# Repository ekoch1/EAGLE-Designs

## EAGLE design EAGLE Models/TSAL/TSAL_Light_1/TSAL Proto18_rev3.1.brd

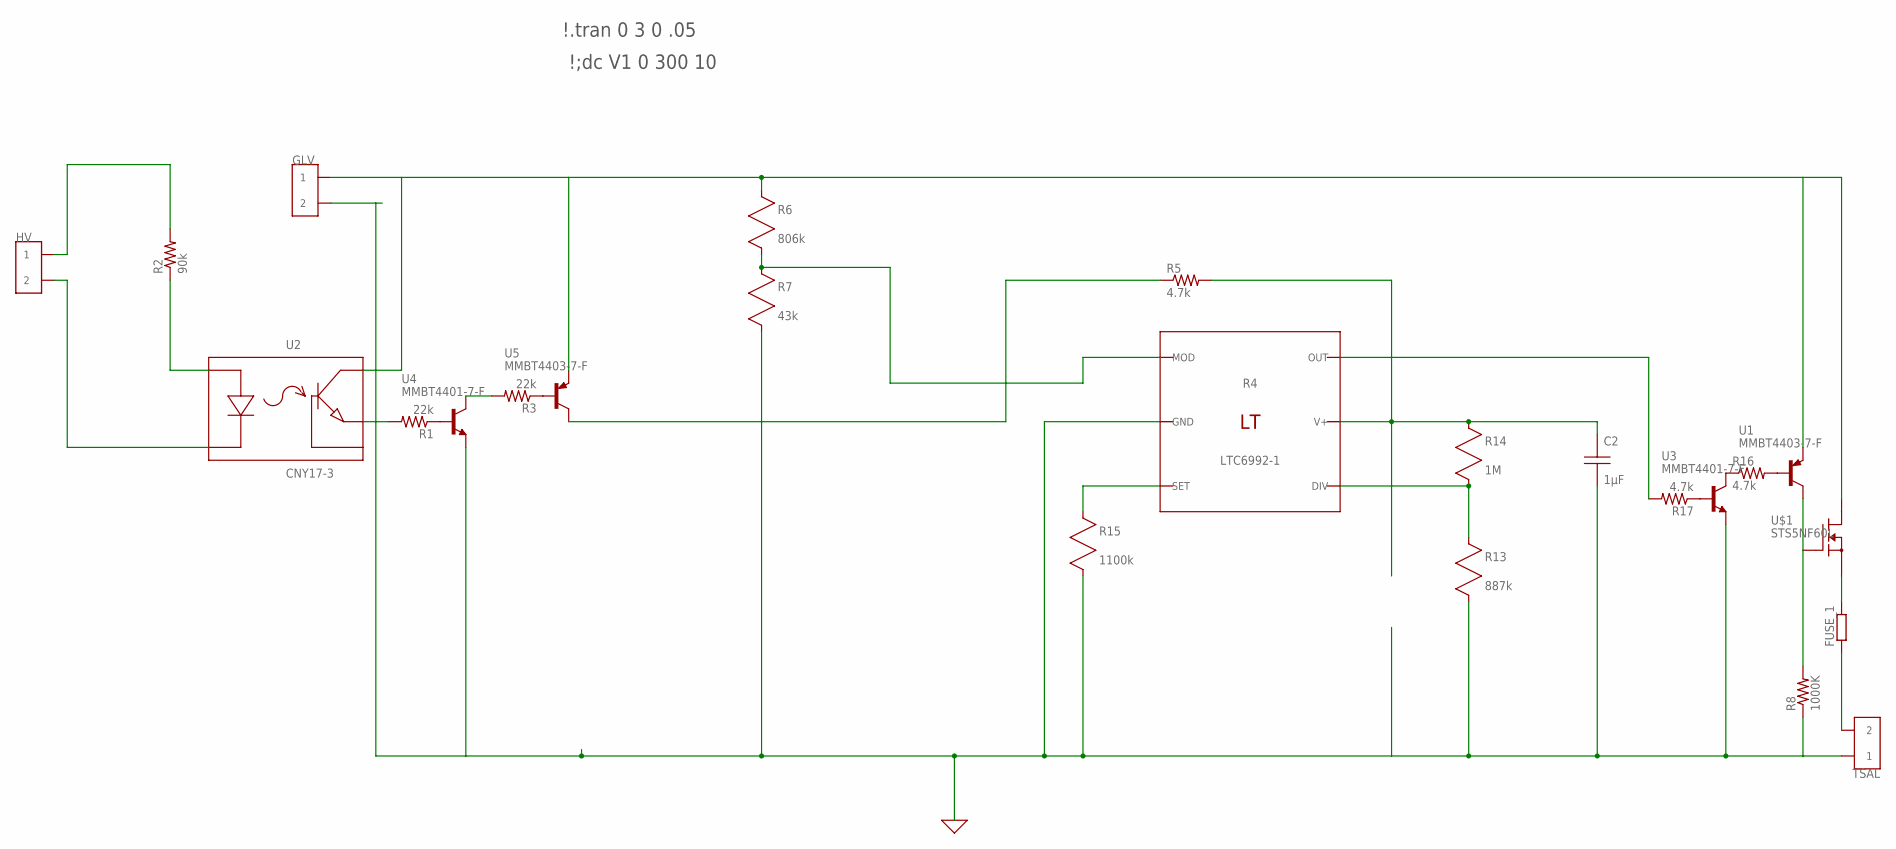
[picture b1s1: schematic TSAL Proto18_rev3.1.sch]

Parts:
C2: 1µF; C0805
FUSE_1: R-EU_R0402; R0402
GLV: CONN_2; CONNECTOR_2
HV: CONN_2; CONNECTOR_2
R1, R3: 22k; R0402
R2: 90k; P0817/22
R4: LTC6992-1
R5: 4.7k; 0805
R6: 806k; R0805
R7: 43k; R0805
R8: 1000K; 0805
R13: 887k; R0805
R14: 1M; R0805
R15: 1100k; R0805
R16, R17: 4.7k; R0402
TSAL: CONN_2; CONNECTOR_2
U1, U5: MMBT4403-7-F; SOT-23-3
U2: CNY17-3
U3, U4: MMBT4401-7-F; SOT-23-3
U$1: STS5NF60L; SO08

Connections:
12V: GLV.1, GLV.2 (1), R6.1 (A), U1.P$3 (E), U2.P$5 (C), U5.P$3 (E), U$1.5 (D), U$1.6 (D), U$1.7 (D), U$1.8 (D)
GND: C2.2 (B), GLV.3 (2), GLV.4 (2), R4.P$2 (GND), R7.2 (B), R8.1, R13.2 (B), R15.2 (B), TSAL.1, TSAL.2 (1), U3.P$3 (E), U4.P$3 (E)
HV+: HV.1, HV.2 (1), R2.2
HV-: HV.3 (2), HV.4 (2), U2.P$2 (K)
unnamed: R1.1, U4.P$2 (B)
unnamed: R3.1, U5.P$2 (B)
unnamed: R3.2, U4.P$1 (C)
unnamed: R1.2, U2.P$4 (E)
unnamed: R5.1, U5.P$1 (C)
unnamed: R8.2, U1.P$1 (C), U$1.4 (G)
unnamed: R4.P$1 (MOD), R6.2 (B), R7.1 (A)
unnamed: R4.P$6 (OUT), R17.2
unnamed: R2.1, U2.P$1 (A)
unnamed: FUSE_1.2, U$1.1 (S), U$1.2 (S), U$1.3 (S)
unnamed: R16.2, U1.P$2 (B)
unnamed: R16.1, U3.P$1 (C)
unnamed: C2.1 (A), R4.P$5 (V+), R5.2, R14.1 (A)
unnamed: R4.P$3 (SET), R15.1 (A)
unnamed: R4.P$4 (DIV), R13.1 (A), R14.2 (B)
unnamed: R17.1, U3.P$2 (B)
TSAL+: FUSE_1.1, TSAL.3 (2), TSAL.4 (2)

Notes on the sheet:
\!;dc V1 0 300 10
\!.tran 0 3 0 .05

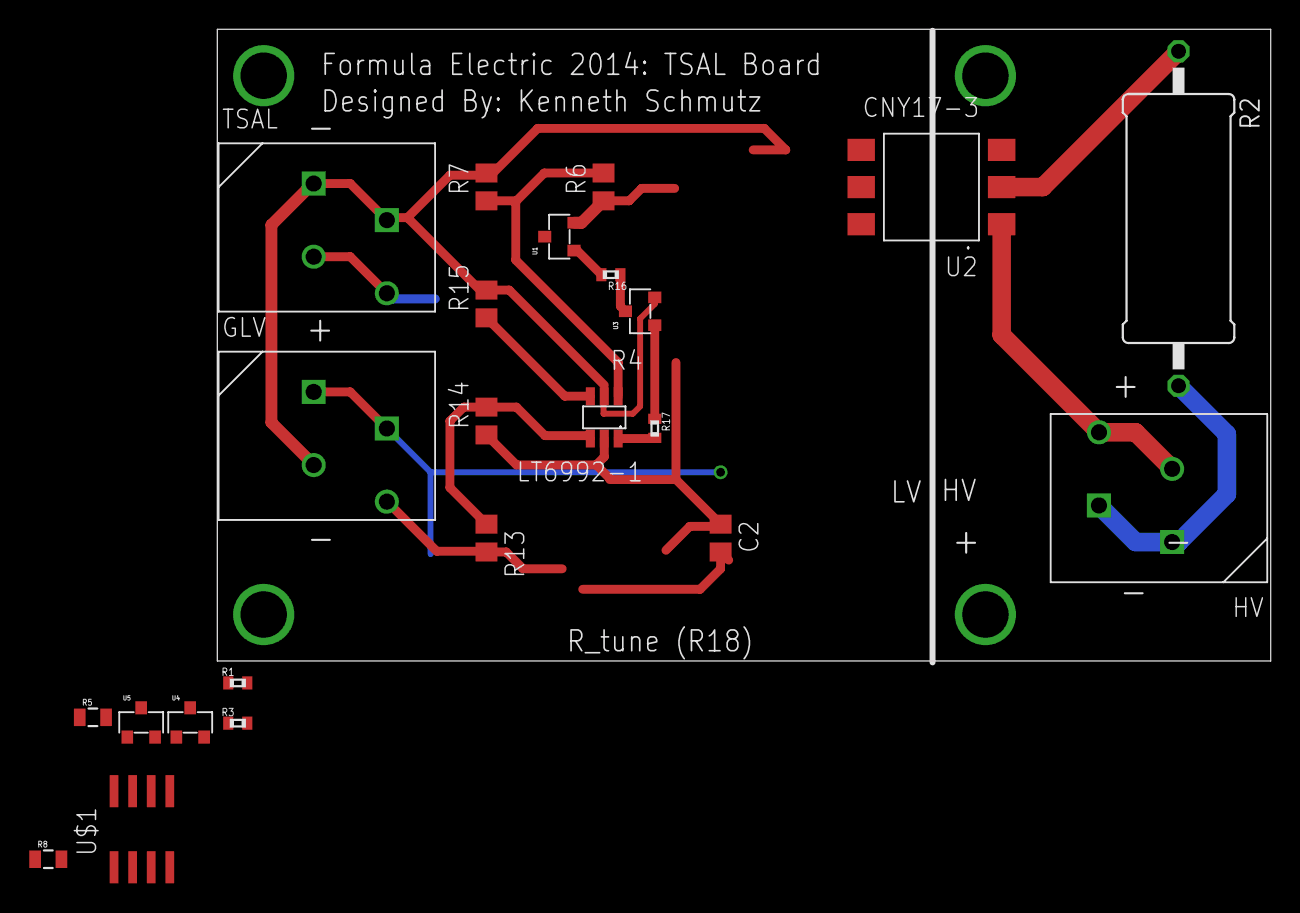
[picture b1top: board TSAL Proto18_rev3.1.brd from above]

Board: 2 copper layers, 72.0 x 43.2 mm, 24 parts (1 on the bottom side), 21 nets.

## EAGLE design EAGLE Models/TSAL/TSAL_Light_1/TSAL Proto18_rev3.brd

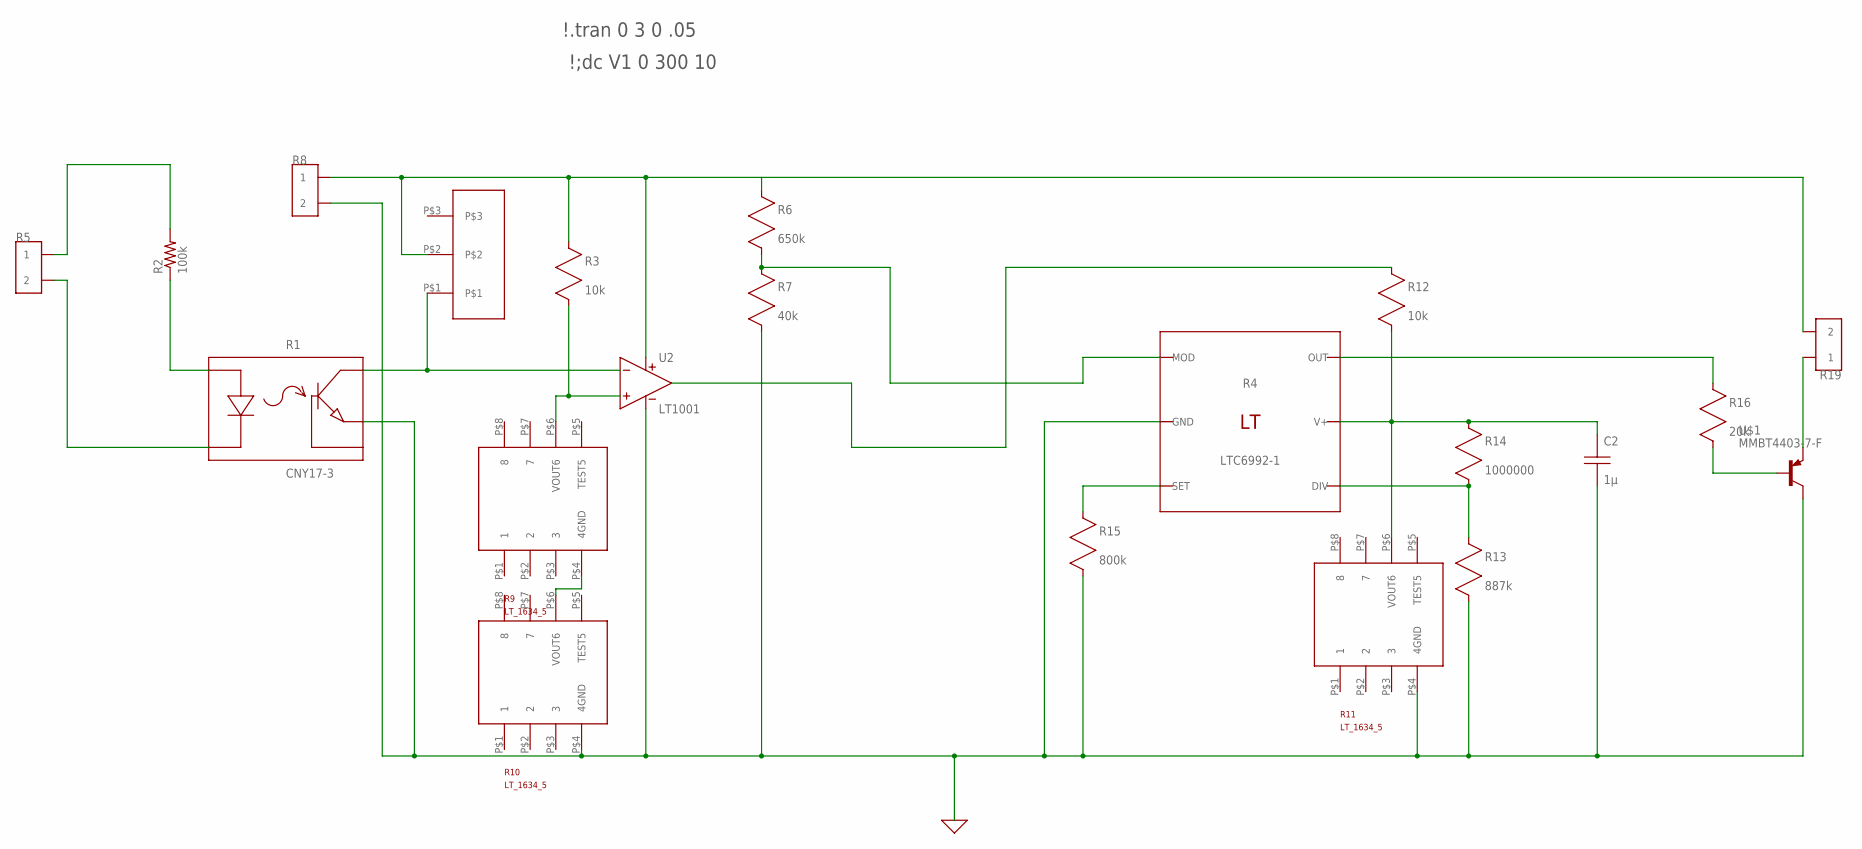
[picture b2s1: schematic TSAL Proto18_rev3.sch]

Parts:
C2: 1µ; C0805
R1: CNY17-3
R2: 100k; P0817/22
R3, R12: 10k; R0805
R4: LTC6992-1
R5, R8, R19: CONN_2; CONNECTOR_2
R6: 650k; R0805
R7: 40k; R0805
R9, R10, R11: LT_1634_5MS8; LT_1634_5
R13: 887k; R0805
R14: 1000000; R0805
R15: 800k; R0805
R16: 20k; R0805
U2: LT1001; S8
U$1: MMBT4403-7-F; SOT-23-3
U$2: RK097111T; RK097-POTENTIOMETER

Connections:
0: C2.2 (B), R1.P$4 (E), R4.P$2 (GND), R7.2 (B), R8.3 (2), R8.4 (2), R10.P$4 (4GND), R11.P$4 (4GND), R13.2 (B), R15.2 (B), U2.4 (V-), U$1.P$1 (C)
unnamed: R2.2, R5.1, R5.2 (1)
unnamed: R1.P$2 (K), R5.3 (2), R5.4 (2)
unnamed: R9.P$4 (4GND), R10.P$6 (VOUT6)
unnamed: R3.1 (A), R6.1 (A), R8.1, R8.2 (1), R19.3 (2), R19.4 (2), U2.8 (V+), U$2.P$2
unnamed: R16.2 (B), U$1.P$2 (B)
unnamed: R12.1 (A), U2.3 (OUT)
unnamed: R4.P$1 (MOD), R6.2 (B), R7.1 (A)
unnamed: R4.P$6 (OUT), R16.1 (A)
unnamed: R1.P$1 (A), R2.1
unnamed: R1.P$5 (C), U2.2 (IN-), U$2.P$1
unnamed: R3.2 (B), R9.P$6 (VOUT6), U2.1 (IN+)
unnamed: R19.1, R19.2 (1), U$1.P$3 (E)
unnamed: C2.1 (A), R4.P$5 (V+), R11.P$6 (VOUT6), R12.2 (B), R14.1 (A)
unnamed: R4.P$3 (SET), R15.1 (A)
unnamed: R4.P$4 (DIV), R13.1 (A), R14.2 (B)

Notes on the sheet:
\!;dc V1 0 300 10
\!.tran 0 3 0 .05

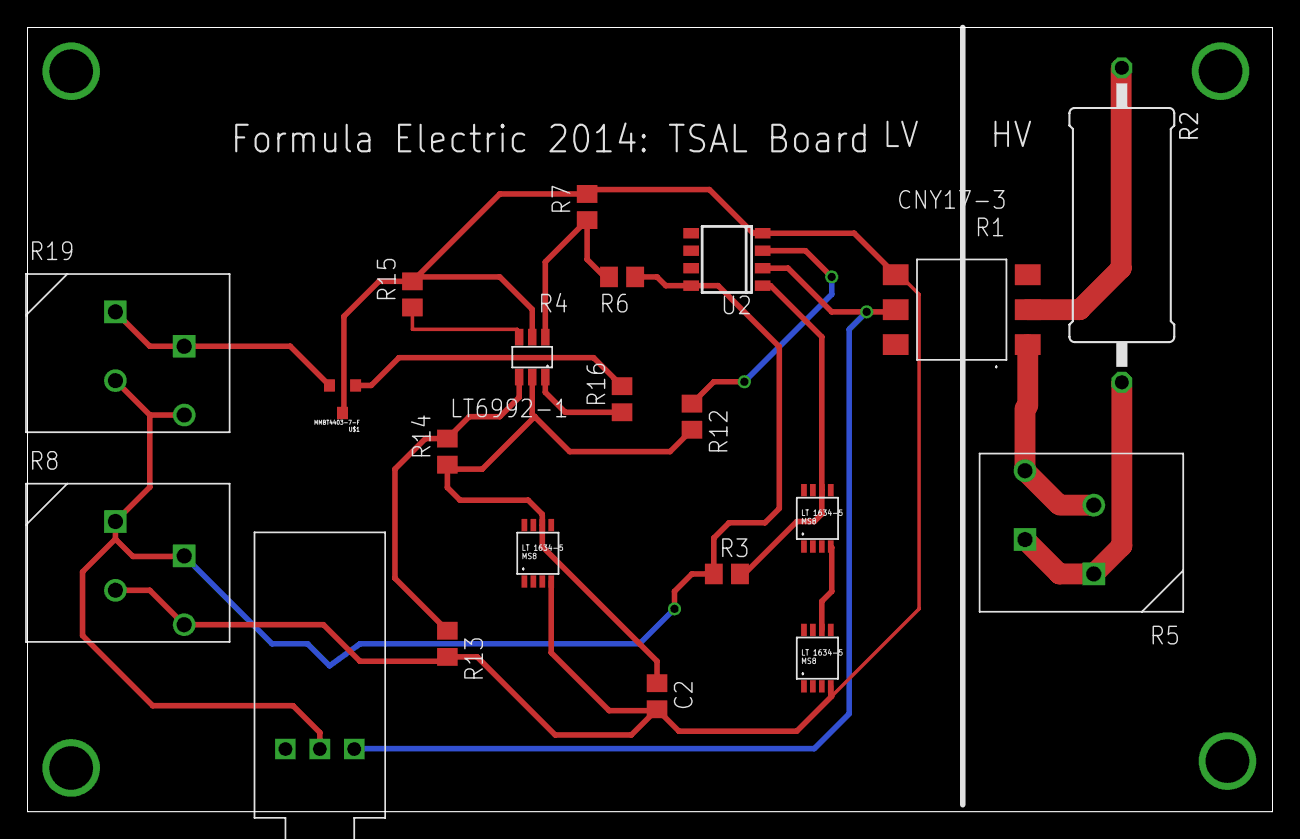
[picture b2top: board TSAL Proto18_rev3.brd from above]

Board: 2 copper layers, 90.5 x 57.0 mm, 21 parts (0 on the bottom side), 16 nets.

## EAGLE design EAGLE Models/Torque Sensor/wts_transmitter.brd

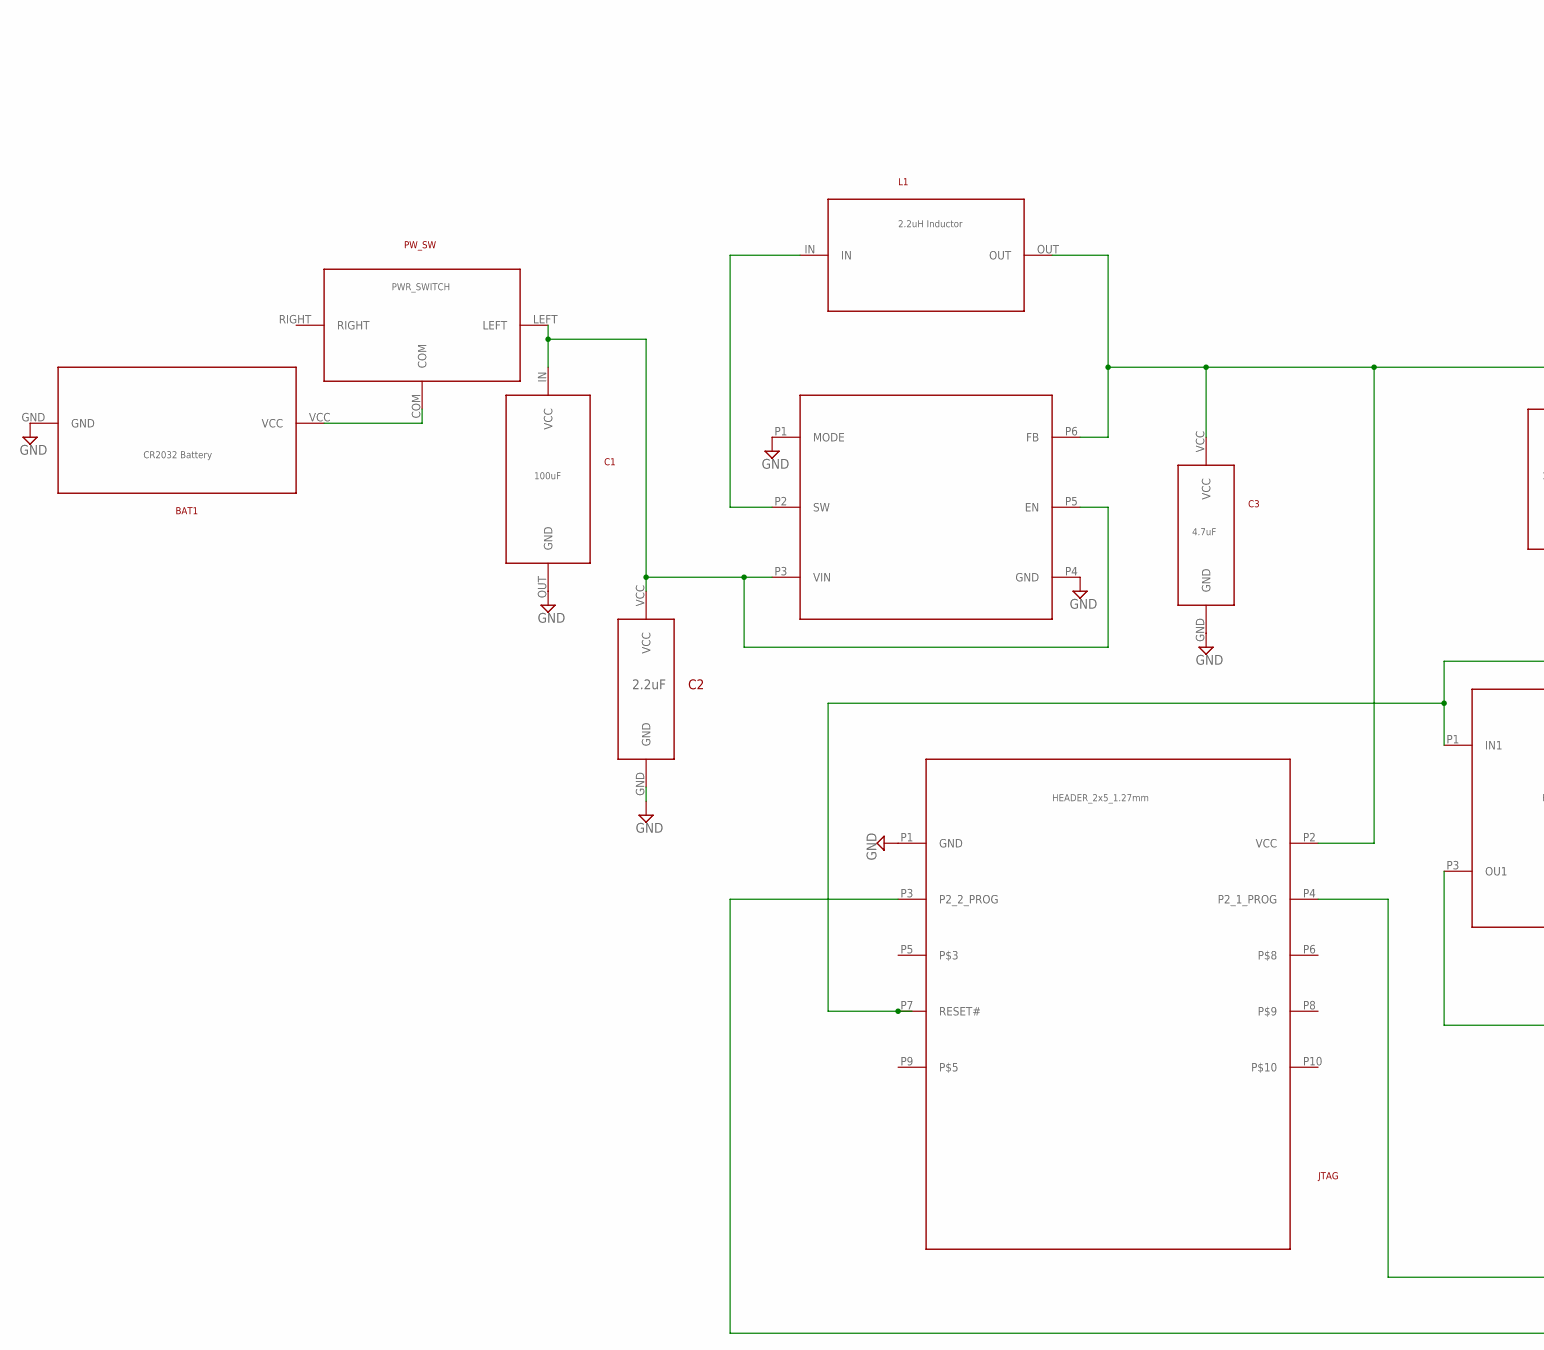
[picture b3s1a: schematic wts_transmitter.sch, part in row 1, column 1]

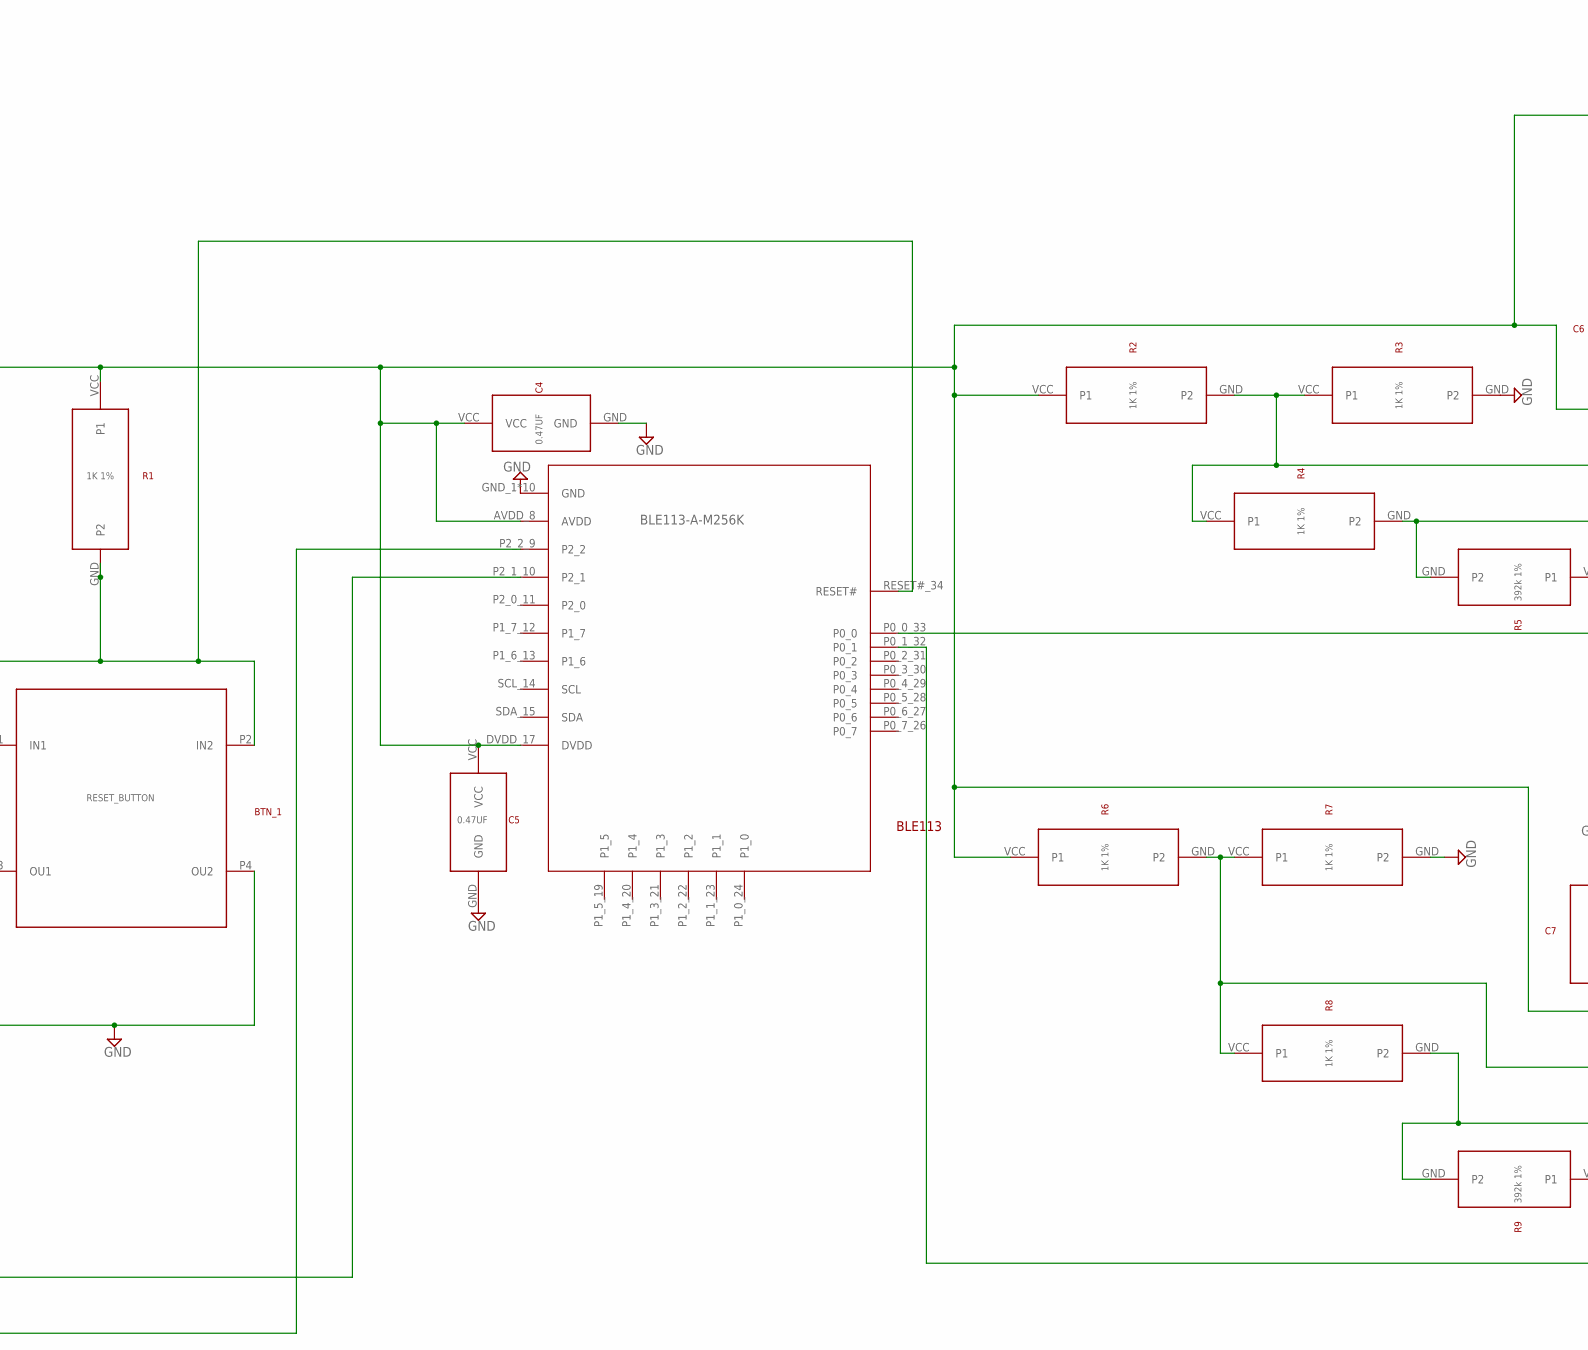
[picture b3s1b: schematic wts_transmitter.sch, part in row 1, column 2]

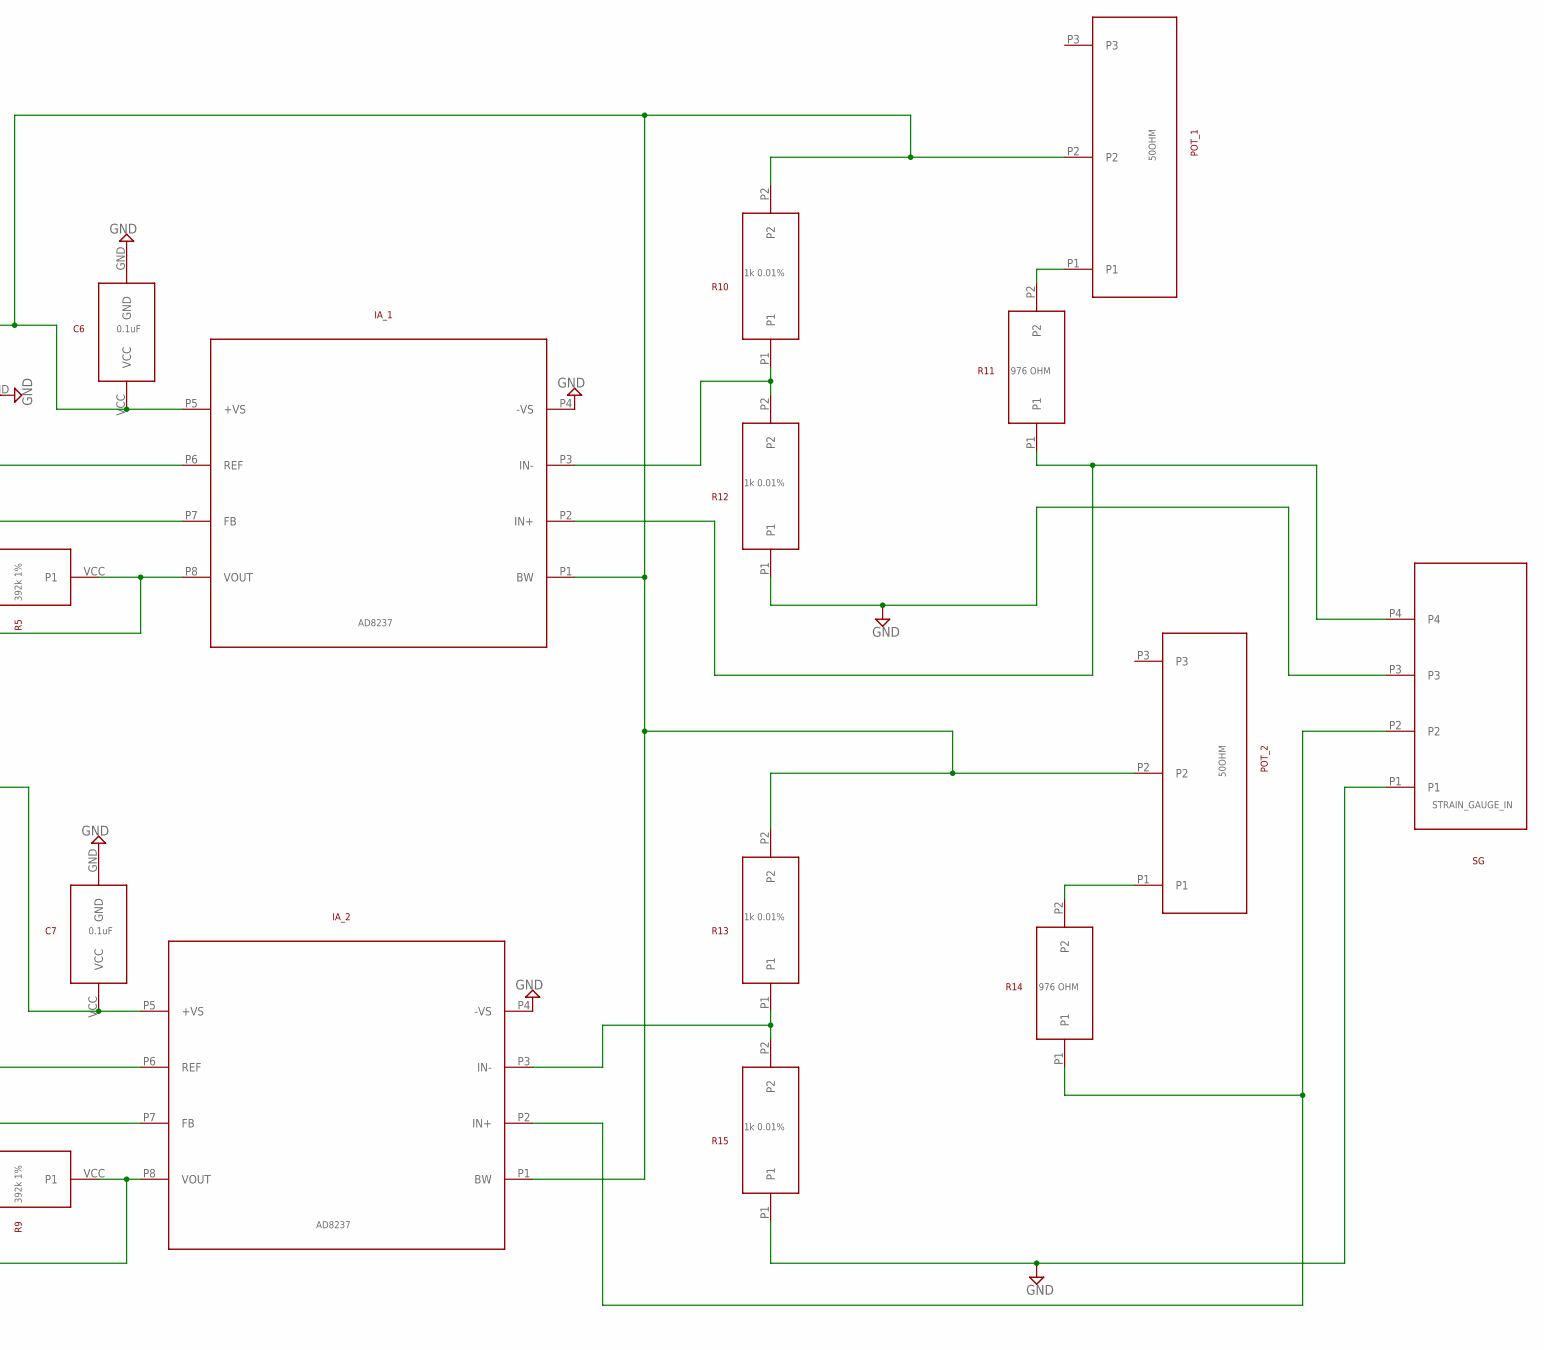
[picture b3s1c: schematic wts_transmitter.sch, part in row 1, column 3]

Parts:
BAT1: CR2032
BLE113: BLE113-A-M256K; BLE113
BTN_1: RESET_BUTTON; RESET_SMT
C1: 100UF_CAP; 1206
C2: 2.2UF_CAP; 0603
C3: 4.7UF_CAP; 0603
C4, C5: 0.47UF_CAP; 0402
C6, C7: 0.1UF_CAP; 0402
DC_DC: TPS62234; DRY6
IA_1, IA_2: AD8237; MSOP8
JTAG: JTAG_HEADER; 1.27MM_2X5_HEADER
L1: 2.2UH_INDUCTOR; 1206
POT_1, POT_2: 50OHM_TRIMPOT; PV36W_TRIMPOT
PW_SW: PWR_SWITCH
R1, R2, R3, R4, R6, R7, R8: 1KOHM_RESISTOR_1%; 0603
R5, R9: 392KOHM_RESISTOR_1%; 0603
R10, R12, R13, R15: 1KOHM_RESISTOR_0.01%; 0805
R11, R14: 976OHM_RESISTOR; 0805
SG: 4_PIN_5.08MM_TERMINAL; 5.08MM_4PIN_HEADER

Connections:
3V: C1.IN (VCC), C2.VCC, DC_DC.P3 (VIN), DC_DC.P5 (EN), PW_SW.LEFT
3V_BAT: BAT1.VCC, PW_SW.COM
GND: BAT1.GND, BLE113.GND_1 (GND), BLE113.GND_2 (GND), BLE113.GND_3 (GND), BLE113.GND_4 (GND), BLE113.GND_5 (GND), BLE113.GND_6 (GND), BLE113.GND_7 (GND), BLE113.GND_18 (GND), BLE113.GND_25 (GND), BLE113.GND_36 (GND), BTN_1.P3 (OU1), BTN_1.P4 (OU2), C1.OUT (GND), C2.GND, C3.GND, C4.GND, C5.GND, C6.GND, C7.GND, DC_DC.P1 (MODE), DC_DC.P4 (GND), IA_1.P4 (-VS), IA_2.P4 (-VS), JTAG.P1 (GND), R3.GND (P2), R7.GND (P2), R12.P1, R15.P1, SG.P1, SG.P3
unnamed: DC_DC.P2 (SW), L1.IN
unnamed: BLE113.P0_0_33 (P0_0), IA_1.P8 (VOUT), R5.VCC (P1)
unnamed: BLE113.P0_1_32 (P0_1), IA_2.P8 (VOUT), R9.VCC (P1)
unnamed: BLE113.P2_2_9 (P2_2), JTAG.P3 (P2_2_PROG)
unnamed: IA_2.P3 (IN-), R13.P1, R15.P2
unnamed: IA_2.P6 (REF), R6.GND (P2), R7.VCC (P1), R8.VCC (P1)
unnamed: IA_2.P7 (FB), R8.GND (P2), R9.GND (P2)
unnamed: BLE113.P2_1_10 (P2_1), JTAG.P4 (P2_1_PROG)
unnamed: BLE113.RESET#_34 (RESET#), BTN_1.P1 (IN1), BTN_1.P2 (IN2), JTAG.P7 (RESET#), R1.GND (P2)
unnamed: IA_1.P6 (REF), R2.GND (P2), R3.VCC (P1), R4.VCC (P1)
unnamed: IA_1.P7 (FB), R4.GND (P2), R5.GND (P2)
unnamed: POT_1.P1, R11.P2
unnamed: IA_1.P3 (IN-), R10.P1, R12.P2
unnamed: IA_1.P2 (IN+), R11.P1, SG.P4
unnamed: POT_2.P1, R14.P2
unnamed: IA_2.P2 (IN+), R14.P1, SG.P2
PWR: BLE113.AVDD_8 (AVDD), BLE113.DVDD_17 (DVDD), C3.VCC, C4.VCC, C5.VCC, C6.VCC, C7.VCC, DC_DC.P6 (FB), IA_1.P1 (BW), IA_1.P5 (+VS), IA_2.P1 (BW), IA_2.P5 (+VS), JTAG.P2 (VCC), L1.OUT, POT_1.P2, POT_2.P2, R1.VCC (P1), R2.VCC (P1), R6.VCC (P1), R10.P2, R13.P2

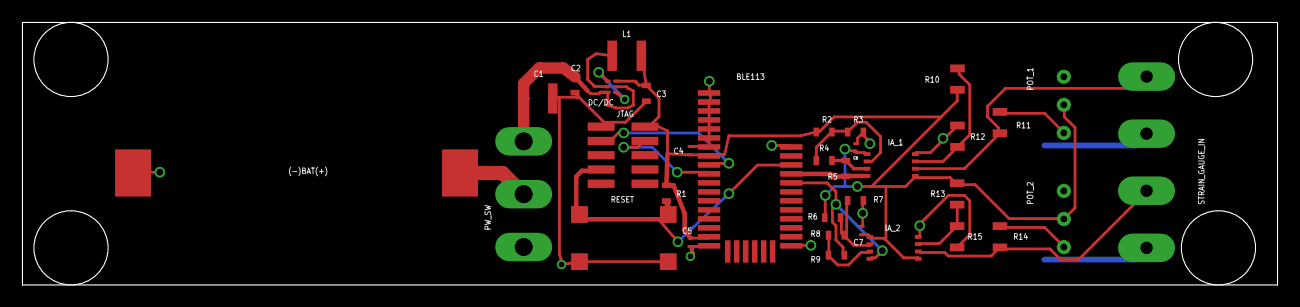
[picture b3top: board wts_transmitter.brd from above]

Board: 2 copper layers, 111.7 x 23.4 mm, 34 parts (0 on the bottom side), 20 nets.

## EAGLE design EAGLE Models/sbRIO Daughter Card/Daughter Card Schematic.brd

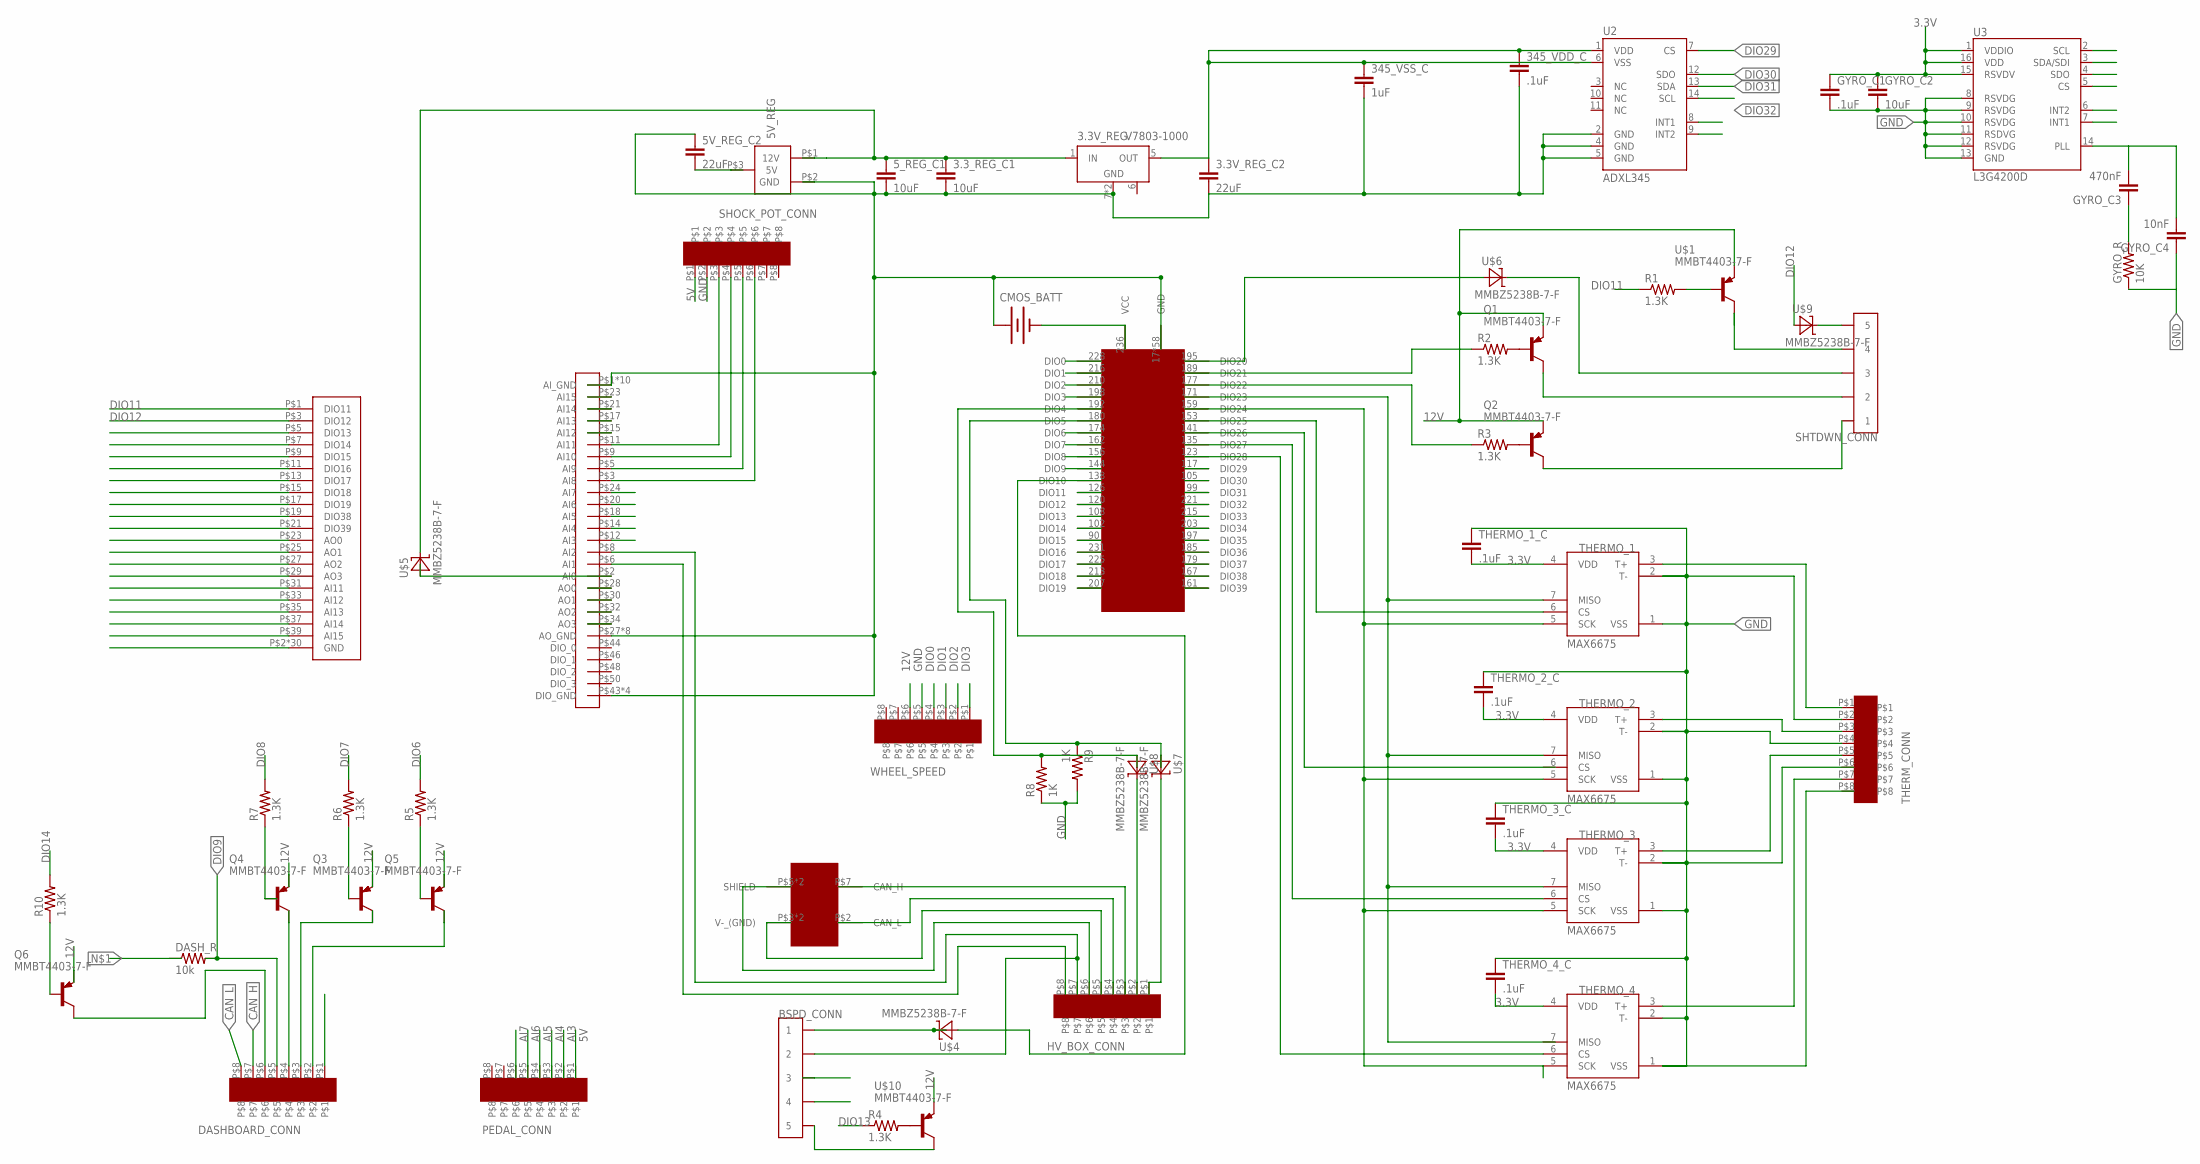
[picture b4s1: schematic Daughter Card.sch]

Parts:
3.3V_REG: V7803-1000; V78XX-1000
3.3V_REG_C2, 5V_REG_C2: 22uF; 0603-CAP
3.3_REG_C1, 5_REG_C1: 10uF; 0603-CAP
5V_REG: V78XX-1500; V78XX-1500R
345_VDD_C: .1uF; 0603-CAP
345_VSS_C: 1uF; 0603-CAP
BSPD_CONN: CONN_5; CONNECTOR_5
CMOS_BATT: BATTERY20PTH; BATTCOM_20MM_PTH
DASHBOARD_CONN: EN3_PCB_8
DASH_R: 10k; 0603-RES
GYRO_C1: .1uF; 0603-CAP
GYRO_C2: 10uF; 0603-CAP
GYRO_C3: 470nF; 0603-CAP
GYRO_C4: 10nF; 0603-CAP
GYRO_R: 10K; 0603-RES
HV_BOX_CONN: EN3_PCB_8
PEDAL_CONN: EN3_PCB_8
Q1, Q2, Q3, Q4, Q5, Q6: MMBT4403-7-F; SOT-23-3
R1, R2, R3, R4, R5, R6, R7, R10: 1.3K; R0402
R8, R9: 1K; R0402
SBRIO_ANALOG: SBRIO_MIO; SBRIO_J502_J503
SBRIO_AUX: SBRIO_AUX; SBRIO_J502_J503
SHOCK_POT_CONN: EN3_PCB_8
SHTDWN_CONN: CONN_5; CONNECTOR_5
THERMO_1, THERMO_2, THERMO_3, THERMO_4: MAX6675; SO08
THERMO_1_C, THERMO_2_C, THERMO_3_C, THERMO_4_C: .1uF; 0603-CAP
THERM_CONN: EN3_PCB_8
U2: ADXL345; LGA14
U3: L3G4200D; LGA16-4X4
U$1, U$10: MMBT4403-7-F; SOT-23-3
U$2: SBRIO_W500; SBRIO_W
U$3: SBRIO_RMC; SEAM-40-XX.X-XX-06-X-A
U$4, U$5, U$6, U$7, U$8, U$9: MMBZ5238B-7-F; SOT-23-3
WHEEL_SPEED: EN3_PCB_8

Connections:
3.3V: 3.3V_REG.5 (OUT), 3.3V_REG_C2.1, 345_VDD_C.1, 345_VSS_C.1, GYRO_C1.1, GYRO_C2.1, THERMO_1.4 (VDD), THERMO_1_C.2, THERMO_2.4 (VDD), THERMO_2_C.2, THERMO_3.4 (VDD), THERMO_3_C.2, THERMO_4.4 (VDD), THERMO_4_C.2, U2.1 (VDD), U2.6 (VSS), U3.1 (VDDIO), U3.15 (RSVDV), U3.16 (VDD)
5V: 5V_REG.P$3 (5V), 5V_REG_C2.2, DASHBOARD_CONN.P$1, PEDAL_CONN.P$1, SHOCK_POT_CONN.P$1
12V: 3.3V_REG.1 (IN), 3.3_REG_C1.1, 5V_REG.P$1 (12V), 5_REG_C1.1, Q1.P$3 (E), Q2.P$3 (E), Q3.P$3 (E), Q4.P$3 (E), Q5.P$3 (E), Q6.P$3 (E), U$1.P$3 (E), U$5.P$1 (C), U$10.P$3 (E), WHEEL_SPEED.P$6
AI3: BSPD_CONN.5 (3), BSPD_CONN.6 (3), PEDAL_CONN.P$2, SBRIO_ANALOG.P$12 (AI3)
AI4: BSPD_CONN.7 (4), BSPD_CONN.8 (4), PEDAL_CONN.P$3, SBRIO_ANALOG.P$14 (AI4)
AI5: PEDAL_CONN.P$4, SBRIO_ANALOG.P$18 (AI5)
AI6: PEDAL_CONN.P$5, SBRIO_ANALOG.P$20 (AI6)
AI7: PEDAL_CONN.P$6, SBRIO_ANALOG.P$24 (AI7)
AI11: SBRIO_ANALOG.P$11 (AI11), SBRIO_AUX.P$31 (AI11), SHOCK_POT_CONN.P$3
AI12: SBRIO_ANALOG.P$15 (AI12), SBRIO_AUX.P$33 (AI12)
AI13: SBRIO_ANALOG.P$17 (AI13), SBRIO_AUX.P$35 (AI13)
AI14: SBRIO_ANALOG.P$21 (AI14), SBRIO_AUX.P$37 (AI14)
AI15: SBRIO_ANALOG.P$23 (AI15), SBRIO_AUX.P$39 (AI15)
AO0: SBRIO_ANALOG.P$28 (AO0), SBRIO_AUX.P$23 (AO0)
AO1: SBRIO_ANALOG.P$30 (AO1), SBRIO_AUX.P$25 (AO1)
AO2: SBRIO_ANALOG.P$32 (AO2), SBRIO_AUX.P$27 (AO2)
AO3: SBRIO_ANALOG.P$34 (AO3), SBRIO_AUX.P$29 (AO3)
CAN_H: DASHBOARD_CONN.P$7, HV_BOX_CONN.P$3, U$2.P$7 (CAN_H)
CAN_L: DASHBOARD_CONN.P$8, HV_BOX_CONN.P$4, U$2.P$2 (CAN_L)
DIO0: U$3.228 (DIO0), WHEEL_SPEED.P$4
DIO1: U$3.216 (DIO1), WHEEL_SPEED.P$3
DIO2: U$3.210 (DIO2), WHEEL_SPEED.P$2
DIO3: U$3.198 (DIO3), WHEEL_SPEED.P$1
DIO6: R5.2, U$3.174 (DIO6)
DIO7: R6.2, U$3.162 (DIO7)
DIO8: R7.2, U$3.156 (DIO8)
DIO9: DASHBOARD_CONN.P$5, DASH_R.2, U$3.144 (DIO9)
DIO11: R1.1, SBRIO_AUX.P$1 (DIO11), U$3.126 (DIO11)
DIO12: SBRIO_AUX.P$3 (DIO12), U$3.120 (DIO12), U$9.P$2 (A)
DIO13: R4.1, SBRIO_AUX.P$5 (DIO13), U$3.108 (DIO13)
DIO14: R10.2, SBRIO_AUX.P$7 (DIO14), U$3.102 (DIO14)
DIO15: SBRIO_AUX.P$9 (DIO15), U$3.90 (DIO15)
DIO16: SBRIO_AUX.P$11 (DIO16), U$3.231 (DIO16)
DIO17: SBRIO_AUX.P$13 (DIO17), U$3.225 (DIO17)
DIO18: SBRIO_AUX.P$15 (DIO18), U$3.213 (DIO18)
DIO19: SBRIO_AUX.P$17 (DIO19), U$3.207 (DIO19)
DIO29: U2.7 (CS), U$3.117 (DIO29)
DIO30: U2.12 (SDO), U3.4 (SDO), U$3.105 (DIO30)
DIO31: U2.13 (SDA), U3.3 (SDA/SDI), U$3.99 (DIO31)
DIO32: U2.14 (SCL), U3.2 (SCL), U$3.221 (DIO32)
DIO33: U3.5 (CS), U$3.215 (DIO33)
DIO34: U3.7 (INT1), U$3.203 (DIO34)
DIO35: U3.6 (INT2), U$3.197 (DIO35)
DIO36: U2.8 (INT1), U$3.185 (DIO36)
DIO37: U2.9 (INT2), U$3.179 (DIO37)
DIO38: SBRIO_AUX.P$19 (DIO38), U$3.167 (DIO38)
DIO39: SBRIO_AUX.P$21 (DIO39), U$3.161 (DIO39)
GND: 3.3V_REG.7 (GND), 3.3V_REG.9 (GND), 3.3V_REG_C2.2, 3.3_REG_C1.2, 5V_REG.P$2 (GND), 5V_REG_C2.1, 5_REG_C1.2, 345_VDD_C.2, 345_VSS_C.2, CMOS_BATT.1 (+), GYRO_C1.2, GYRO_C2.2, GYRO_C4.1, GYRO_R.1, R8.1, R9.2, SBRIO_ANALOG.P$1 (AI_GND), SBRIO_ANALOG.P$4 (AI_GND), SBRIO_ANALOG.P$7 (AI_GND), SBRIO_ANALOG.P$10 (AI_GND), SBRIO_ANALOG.P$13 (AI_GND), SBRIO_ANALOG.P$16 (AI_GND), SBRIO_ANALOG.P$19 (AI_GND), SBRIO_ANALOG.P$22 (AI_GND), SBRIO_ANALOG.P$25 (AI_GND), SBRIO_ANALOG.P$26 (AI_GND), SBRIO_ANALOG.P$27 (AO_GND), SBRIO_ANALOG.P$29 (AO_GND), SBRIO_ANALOG.P$31 (AO_GND), SBRIO_ANALOG.P$33 (AO_GND), SBRIO_ANALOG.P$35 (AO_GND), SBRIO_ANALOG.P$37 (AO_GND), SBRIO_ANALOG.P$39 (AO_GND), SBRIO_ANALOG.P$41 (AO_GND), SBRIO_ANALOG.P$43 (DIO_GND), SBRIO_ANALOG.P$45 (DIO_GND), SBRIO_ANALOG.P$47 (DIO_GND), SBRIO_ANALOG.P$49 (DIO_GND), SBRIO_AUX.P$2 (GND), SBRIO_AUX.P$4 (GND), SBRIO_AUX.P$6 (GND), SBRIO_AUX.P$8 (GND), SBRIO_AUX.P$10 (GND), SBRIO_AUX.P$12 (GND), SBRIO_AUX.P$14 (GND), SBRIO_AUX.P$16 (GND), SBRIO_AUX.P$18 (GND), SBRIO_AUX.P$20 (GND), SBRIO_AUX.P$22 (GND), SBRIO_AUX.P$24 (GND), SBRIO_AUX.P$26 (GND), SBRIO_AUX.P$28 (GND), SBRIO_AUX.P$30 (GND), SBRIO_AUX.P$32 (GND), SBRIO_AUX.P$34 (GND), SBRIO_AUX.P$36 (GND), SBRIO_AUX.P$38 (GND), SBRIO_AUX.P$40 (GND), SBRIO_AUX.P$41 (GND), SBRIO_AUX.P$42 (GND), SBRIO_AUX.P$43 (GND), SBRIO_AUX.P$44 (GND), SBRIO_AUX.P$45 (GND), SBRIO_AUX.P$46 (GND), SBRIO_AUX.P$47 (GND), SBRIO_AUX.P$48 (GND), SBRIO_AUX.P$49 (GND), SBRIO_AUX.P$50 (GND), SHOCK_POT_CONN.P$2, THERMO_1.1 (VSS), THERMO_1.2 (T-), THERMO_1_C.1, THERMO_2.1 (VSS), THERMO_2.2 (T-), THERMO_2_C.1, THERMO_3.1 (VSS), THERMO_3.2 (T-), THERMO_3_C.1, THERMO_4.1 (VSS), THERMO_4.2 (T-), THERMO_4_C.1, THERM_CONN.P$2, THERM_CONN.P$4, U2.2 (GND), U2.4 (GND), U2.5 (GND), U3.8 (RSVDG), U3.9 (RSVDG), U3.10 (RSVDG), U3.11 (RSDVG), U3.12 (RSVDG), U3.13 (GND), U$3.17 (GND), U$3.23 (GND), U$3.30 (GND), U$3.36 (GND), U$3.41 (GND), U$3.47 (GND), U$3.78 (GND), U$3.83 (GND), U$3.88 (GND), U$3.93 (GND), U$3.96 (GND), U$3.98 (GND), U$3.101 (GND), U$3.103 (GND), U$3.106 (GND), U$3.111 (GND), U$3.114 (GND), U$3.116 (GND), U$3.119 (GND), U$3.121 (GND), U$3.124 (GND), U$3.129 (GND), U$3.132 (GND), U$3.134 (GND), U$3.137 (GND), U$3.139 (GND), U$3.142 (GND), U$3.147 (GND), U$3.150 (GND), U$3.152 (GND), U$3.155 (GND), U$3.157 (GND), U$3.160 (GND), U$3.165 (GND), U$3.168 (GND), U$3.170 (GND), U$3.173 (GND), U$3.175 (GND), U$3.178 (GND), U$3.183 (GND), U$3.186 (GND), U$3.188 (GND), U$3.191 (GND), U$3.193 (GND), U$3.196 (GND), U$3.201 (GND), U$3.204 (GND), U$3.206 (GND), U$3.209 (GND), U$3.211 (GND), U$3.214 (GND), U$3.219 (GND), U$3.222 (GND), U$3.224 (GND), U$3.227 (GND), U$3.229 (GND), U$3.232 (GND), U$3.237 (GND), WHEEL_SPEED.P$5
N$: Q4.P$2 (B), R7.1
unnamed: CMOS_BATT.2 (-), U$3.236 (VCC)
unnamed: DASHBOARD_CONN.P$6, Q6.P$1 (C)
unnamed: SBRIO_ANALOG.P$2 (AI0), U$5.P$2 (A)
unnamed: Q6.P$2 (B), R10.1
unnamed: Q1.P$1 (C), SHTDWN_CONN.3 (2), SHTDWN_CONN.4 (2)
unnamed: Q2.P$1 (C), SHTDWN_CONN.1, SHTDWN_CONN.2 (1)
unnamed: SHTDWN_CONN.5 (3), SHTDWN_CONN.6 (3), U$6.P$1 (C)
unnamed: U$3.195 (DIO20), U$6.P$2 (A)
unnamed: R2.1, U$3.189 (DIO21)
unnamed: R3.1, U$3.177 (DIO22)
unnamed: HV_BOX_CONN.P$1, U$7.P$1 (C)
unnamed: HV_BOX_CONN.P$2, U$8.P$1 (C)
unnamed: R8.2, U$3.192 (DIO4), U$8.P$2 (A)
unnamed: R9.1, U$3.180 (DIO5), U$7.P$2 (A)
unnamed: THERMO_1.7 (MISO), THERMO_2.7 (MISO), THERMO_3.7 (MISO), U$3.171 (DIO23)
unnamed: THERMO_1.5 (SCK), THERMO_2.5 (SCK), THERMO_3.5 (SCK), U$3.159 (DIO24)
unnamed: HV_BOX_CONN.P$5, U$2.P$3 (V-_(GND)), U$2.P$6 (V-_(GND))
unnamed: HV_BOX_CONN.P$8, SBRIO_ANALOG.P$6 (AI1)
unnamed: BSPD_CONN.3 (2), BSPD_CONN.4 (2), HV_BOX_CONN.P$7, SBRIO_ANALOG.P$8 (AI2)
unnamed: DASHBOARD_CONN.P$2, Q5.P$1 (C)
unnamed: DASHBOARD_CONN.P$3, Q3.P$1 (C)
unnamed: DASHBOARD_CONN.P$4, Q4.P$1 (C)
unnamed: THERMO_1.6 (CS), U$3.153 (DIO25)
unnamed: THERMO_3.6 (CS), U$3.135 (DIO27)
unnamed: THERMO_4.6 (CS), U$3.123 (DIO28)
unnamed: THERMO_1.3 (T+), THERM_CONN.P$1
unnamed: THERMO_2.3 (T+), THERM_CONN.P$3
unnamed: THERMO_3.3 (T+), THERM_CONN.P$5
unnamed: THERMO_4.3 (T+), THERM_CONN.P$7
unnamed: SHTDWN_CONN.9 (5), SHTDWN_CONN.10 (5), U$9.P$1 (C)
unnamed: SBRIO_ANALOG.P$9 (AI10), SHOCK_POT_CONN.P$4
unnamed: SBRIO_ANALOG.P$5 (AI9), SHOCK_POT_CONN.P$5
unnamed: SBRIO_ANALOG.P$3 (AI8), SHOCK_POT_CONN.P$6
unnamed: GYRO_C3.2, GYRO_C4.2, U3.14 (PLL)
unnamed: GYRO_C3.1, GYRO_R.2
unnamed: BSPD_CONN.1, BSPD_CONN.2 (1), U$4.P$1 (C)
unnamed: U$3.138 (DIO10), U$4.P$2 (A)
unnamed: SHTDWN_CONN.7 (4), SHTDWN_CONN.8 (4), U$1.P$1 (C)
unnamed: BSPD_CONN.9 (5), BSPD_CONN.10 (5), U$10.P$1 (C)
unnamed: R1.2, U$1.P$2 (B)
unnamed: Q1.P$2 (B), R2.2
unnamed: Q2.P$2 (B), R3.2
unnamed: R4.2, U$10.P$2 (B)
unnamed: Q5.P$2 (B), R5.1
unnamed: Q3.P$2 (B), R6.1
SHIELD: HV_BOX_CONN.P$6, U$2.P$5 (SHIELD), U$2.P$10 (SHIELD)

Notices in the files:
parts and their libraries:
SparkFun-Passives: Licensing: CC v3.0 Share-Alike You are welcome to use this library for commercial purposes.
